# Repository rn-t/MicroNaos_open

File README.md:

# MicroNaos_open
マイクロマウスというロボット競技の、クラシックマウス部門用のロボットです。

## ディレクトリ
### DXF

基板外形のDXFファイルです

### firmware
STM32向けのソースコードです。主にC++で記述しています。STM32HAL、CMSIS、SEGGER-RTTなどのライブラリも含まれています。

### PCB
機体の大部分を構成しているプリント基板及び、その回路のファイルです。Kicadを用いて作成しました
公開するにあたってライセンスの問題がないように編集を行ったため、回路シンボルが基板発注時と少し異なっています。

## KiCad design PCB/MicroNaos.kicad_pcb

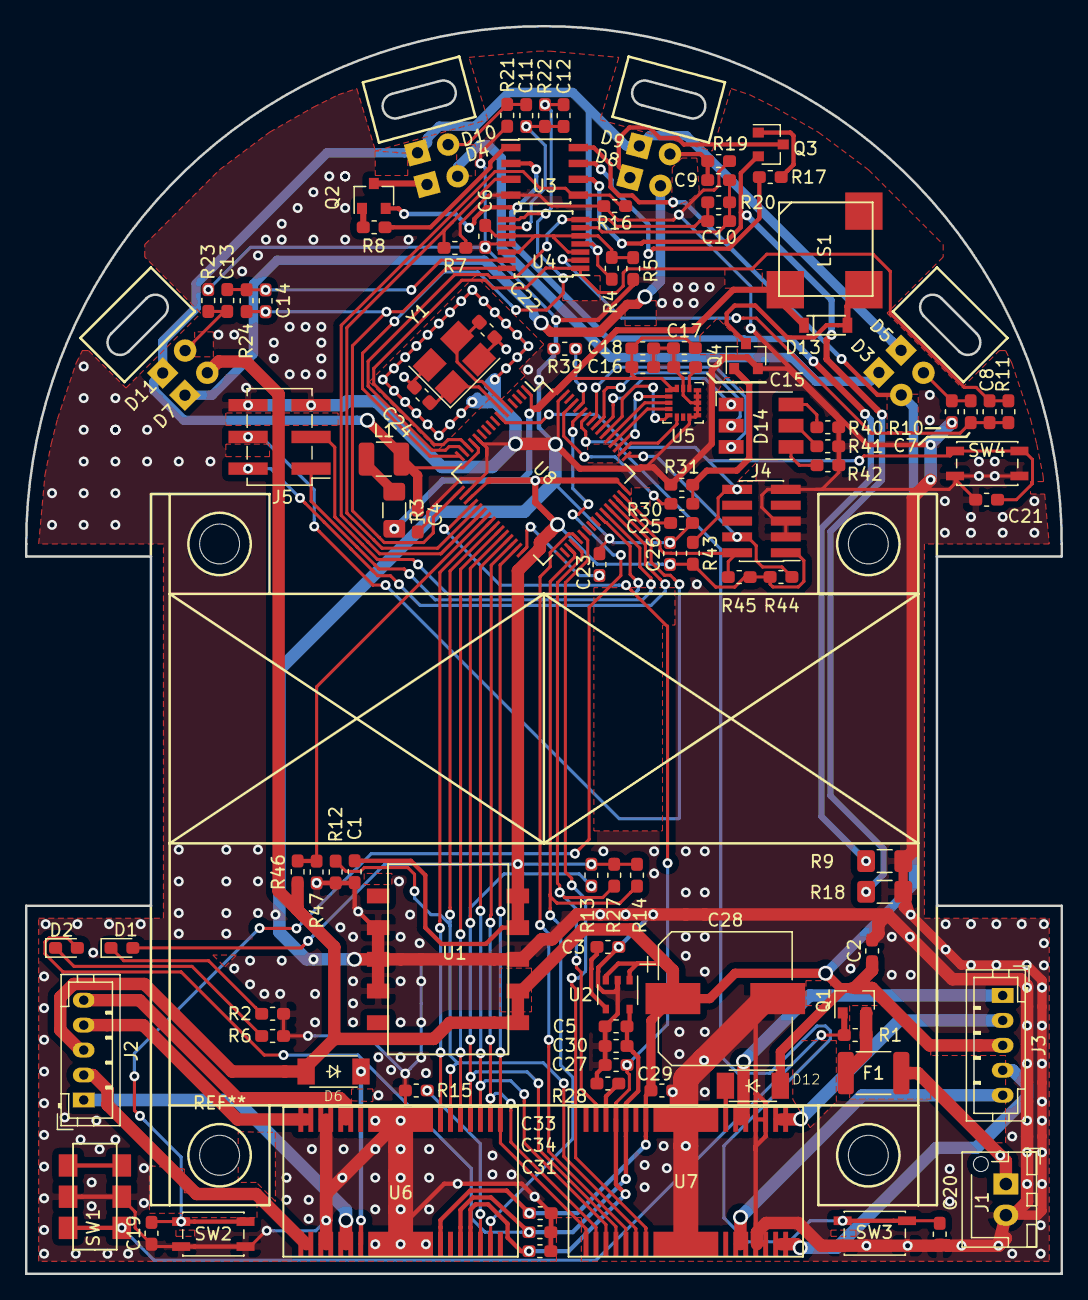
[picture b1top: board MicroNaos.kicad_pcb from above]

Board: 2 copper layers, 83.0 x 100.0 mm, 109 parts (0 on the bottom side), 91 nets.

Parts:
C1: 3.3u; C_0603_1608Metric_Pad1.05x0.95mm_HandSolder
C2: 1u; C_0603_1608Metric_Pad1.05x0.95mm_HandSolder
C3, C7, C9, C11, C13, C16: 0.01u; C_0603_1608Metric_Pad1.05x0.95mm_HandSolder
C4, C5: 10u; C_0603_1608Metric_Pad1.05x0.95mm_HandSolder
C6, C15, C17, C19, C20, C21, C26: 0.1u; C_0603_1608Metric_Pad1.05x0.95mm_HandSolder
C8, C10, C12, C14: 22p; C_0603_1608Metric_Pad1.05x0.95mm_HandSolder
C18, C23, C25: 2.2u; C_0603_1608Metric_Pad1.05x0.95mm_HandSolder
C22, C24: 10p; C_0603_1608Metric_Pad1.05x0.95mm_HandSolder
C27, C29, C30, C31, C33, C34: 0.1uF; C_0603_1608Metric_Pad1.05x0.95mm_HandSolder
C28: 100uF; CP_Elec_10x10.5
D1: LED_3.3V; LED_0603_1608Metric_Pad1.05x0.95mm_HandSolder
D2: LED_5V; LED_0603_1608Metric_Pad1.05x0.95mm_HandSolder
D3, D4, D7, D8: VSLY5850; LED_D5.0mm_Sensor
D5, D9, D10, D11: SFH213FA; LED_D5.0mm_Sensor
D6, D12: 24V1W; SOD128
D13: GS1010FL; SOD-123FL
D14: OSTBABS4C2B; LED_RGB_5050-6
F1: SMD1812P150TF/24; Fuse_1812_4532Metric_Pad1.30x3.40mm_HandSolder
J1: BATTERY; JST_XH_B02B-XH-AM_1x02_P2.50mm_Vertical
J2, J3: PH_5Pin; JST_PH_B5B-PH-K_1x05_P2.00mm_Vertical
J4: Conn_ARM_JTAG_SWD_10; PinHeader_2x05_P1.27mm_Vertical_SMD
J5: Conn_02x03_Odd_Even; PinHeader_2x03_P2.54mm_Vertical_SMD
L1: 100u; L_1210_3225Metric
LS1: Speaker; UGCT7525AN4
Q1: IRLML6402; SOT-23
Q2, Q3, Q4: IRFML8244; SOT-23
R1, R10, R19, R21, R23: 100k; R_0603_1608Metric_Pad1.05x0.95mm_HandSolder
R2, R6: 1k; R_0603_1608Metric_Pad1.05x0.95mm_HandSolder
R3: 10; R_1206_3216Metric_Pad1.42x1.75mm_HandSolder
R4, R5: 1k 1%; R_0603_1608Metric_Pad1.05x0.95mm_HandSolder
R7, R12, R13, R14, R15, R16, R27, R28, R31, R39, R43, R44, R45, R47: 10k; R_0603_1608Metric_Pad1.05x0.95mm_HandSolder
R8, R17: 10; R_0603_1608Metric_Pad1.05x0.95mm_HandSolder
R9, R18: 33 1% 1/2W; R_1206_3216Metric_Pad1.42x1.75mm_HandSolder
R11, R20, R22, R24: 220k; R_0603_1608Metric_Pad1.05x0.95mm_HandSolder
R30: 100; R_0603_1608Metric_Pad1.05x0.95mm_HandSolder
R40, R41, R42: 330; R_0603_1608Metric_Pad1.05x0.95mm_HandSolder
R46: 33k; R_0603_1608Metric_Pad1.05x0.95mm_HandSolder
SW1: SSSS213202
SW2, SW3, SW4: SKRPACE010; SW_SPST_EVQP2
U1: M78SAR033-0.5
U2: TAR5SB50; TSOP-5_1.65x3.05mm_P0.95mm
U3: NJM2746E; SOIC-8_3.9x4.9mm_P1.27mm
U4: AD8604A; TSSOP-14_4.4x5mm_P0.65mm
U5: ICM-20602; LGA-16_3x3mm_P0.5mm_LayoutBorder3x5y
U6, U7: TB67S149FG; HSOP28-P-0450-0.80
U8: STM32F405RGTx; LQFP-64_10x10mm_P0.5mm
Y1: 12MHz; Crystal_SMD_SeikoEpson_FA238V-4Pin_3.2x2.5mm_HandSoldering

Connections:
1.65V: C6.1, R4.2, R5.1, U4.3 (+), U4.5 (+), U4.10 (+), U4.12 (+)
3.3V: C1.1, C16.1, C17.1, C18.1, C26.2, D1.2 (A), D13.1 (K), J4.1 (VTref), LS1.1, R3.2, R13.1, R14.1, R27.1, R43.1, R44.1, R45.1, U1.4 (Vout), U1.5 (Vout), U5.1 (VDDIO), U5.16 (VDD), U8.1 (VBAT), U8.19 (VDD), U8.32 (VDD), U8.48 (VDD), U8.64 (VDD)
3.3VA: C4.1, D5.1 (K), D9.1 (K), D10.1 (K), D11.1 (K), L1.2, R4.1, U4.4 (V+), U8.13 (VDDA)
5V: C5.1, C30.1, C34.1, D2.2 (A), U2.5 (Vout), U6.24 (VCC), U7.24 (VCC)
/Gyro/CS: U5.5 (~CS), U8.54 (PD2)
/Gyro/INT: U5.6 (INT), U8.50 (PA15)
/Gyro/SDI: U5.3 (SDA/SDI), U8.53 (PC12)
/Gyro/SDO: U5.4 (SAO/SD0), U8.52 (PC11)
/Gyro/SPC: U5.2 (SCL/SPC), U8.51 (PC10)
/IR_LED1/LED_IN: R7.2, U3.3 (+), U8.21 (PA5)
/IR_LED2/LED_IN: R16.2, U3.5 (+), U8.22 (PA6)
/IR_Sensor1/SENSOR_OUT: C8.1, R11.1, U4.1, U8.14 (PA0)
/IR_Sensor2/SENSOR_OUT: C10.1, R20.1, U4.7, U8.15 (PA1)
/IR_Sensor3/SENSOR_OUT: C12.1, R22.1, U4.8, U8.16 (PA2)
/IR_Sensor4/SENSOR_OUT: C14.1, R24.1, U4.14, U8.17 (PA3)
/Micon/BATT_CHECK: R46.2, R47.1, U8.23 (PA7)
/Micon/DAC: C27.1, C31.1, U6.25 (VREF), U7.25 (VREF), U8.20 (PA4)
/Micon/MOTOR1_CW: U6.7 (CW/CCW), U8.24 (PC4)
/Micon/MOTOR1_ERR: R14.2, U6.27 (ERR), U8.35 (PB14)
/Micon/MOTOR1_PWM: U6.5 (CLK), U8.26 (PB0)
/Micon/MOTOR2_CW: U7.7 (CW/CCW), U8.38 (PC7)
/Micon/MOTOR2_ERR: R27.2, U7.27 (ERR), U8.36 (PB15)
/Micon/MOTOR2_PWM: U7.5 (CLK), U8.37 (PC6)
/Micon/MOTOR_DMODE0: U6.1 (DMODE0), U7.1 (DMODE0), U8.30 (PB11)
/Micon/MOTOR_DMODE1: U6.2 (DMODE1), U7.2 (DMODE1), U8.29 (PB10)
/Micon/MOTOR_DMODE2: U6.3 (DMODE2), U7.3 (DMODE2), U8.28 (PB2)
/Micon/MOTOR_EN: R12.1, U6.6 (ENABLE), U7.6 (ENABLE), U8.25 (PC5)
/Micon/MOTOR_RESET: R13.2, U6.4 (RESET), U7.4 (RESET), U8.27 (PB1)
/Micon/NRST: C21.2, J4.10 (~RESET), R43.2, SW4.1, U8.7 (NRST)
/Micon/PB8_SPEAKER: R30.2, U8.61 (PB8)
/Micon/SWCLK: J4.4 (SWDCLK/TCK), R44.2, U8.49 (PA14)
/Micon/SWDIO: J4.2 (SWDIO/TMS), R45.2, U8.46 (PA13)
/Micon/SW_1: C20.2, SW3.1, U8.58 (PB6)
/Micon/SW_2: C19.2, SW2.1, U8.59 (PB7)
/Micon/UART_RX: J5.1, U8.43 (PA10)
/Micon/UART_TX: J5.3, U8.42 (PA9)
/Micon/USB_DM: J5.2, U8.44 (PA11)
/Micon/USB_DP: J5.4, U8.45 (PA12)
BATT: C2.1, C28.1, C29.1, C33.1, D3.2 (A), D6.2 (A), D7.2 (A), D12.2 (A), J2.3, J3.3, Q1.3 (D), R46.1, U1.1 (Vin), U1.2 (Vin), U2.1 (Vin), U2.3 (Control), U3.8 (V+), U6.22 (VM), U7.22 (VM)
GND: C1.2, C2.2, C3.2, C4.2, C5.2, C6.2, C15.2, C16.2, C17.2, C18.2, C19.1, C20.1, C21.1, C22.2, C23.1, C24.2, C25.1, C26.1, C27.2, C28.2, C29.2, C30.2, C31.2, C33.2, C34.2, J1.2, J4.3 (GND), J4.5 (GND), J4.9 (GNDDetect), J5.5, J5.6, Q4.2 (S), R2.2, R5.2, R6.2, R7.1, R9.2, R10.1, R12.2, R15.2, R16.1, R18.2, R19.1, R21.1, R23.1, R28.2, R31.1, R39.2, R40.1, R41.1, R42.1, R47.2, SW1.2 (B), SW2.2, SW3.2, SW4.2, U1.3 (GND), U1.7 (GND), U1.8 (GND), U1.9 (GND), U2.2 (GND), U3.4 (V-), U4.11 (V-), U5.8 (FSYNC), U5.9 (GND), U5.10 (GND), U5.11 (GND), U5.12 (GND), U5.13 (GND), U5.15 (GND), U6.11 (RSGNDA), U6.12 (RSGNDA), U6.17 (RSGNDB), U6.18 (RSGNDB), U6.FIN1 (GND), U6.FIN2 (GND), U7.11 (RSGNDA), U7.12 (RSGNDA), U7.17 (RSGNDB), U7.18 (RSGNDB), U7.FIN1 (GND), U7.FIN2 (GND), U8.12 (VSSA), U8.18 (VSS), U8.63 (VSS), Y1.2, Y1.4
unnamed: C3.1, U2.4 (Noise)
unnamed: C7.1, C8.2, R11.2, U4.2 (-)
unnamed: C7.2, D5.2 (A), R10.2
unnamed: C9.2, D9.2 (A), R19.2
unnamed: C9.1, C10.2, R20.2, U4.6 (-)
unnamed: C11.1, C12.2, R22.2, U4.9 (-)
unnamed: C11.2, D10.2 (A), R21.2
unnamed: C13.1, C14.2, R24.2, U4.13 (-)
unnamed: C13.2, D11.2 (A), R23.2
unnamed: C15.1, U5.14 (REGOUT)
unnamed: C22.1, U8.5 (PH0), Y1.3
unnamed: C23.2, U8.31 (VCAP_1)
unnamed: C24.1, U8.6 (PH1), Y1.1
unnamed: C25.2, U8.47 (VCAP_2)
unnamed: D1.1 (K), R2.1
unnamed: D2.1 (K), R6.1
unnamed: D3.1 (K), D4.2 (A)
unnamed: D4.1 (K), Q2.3 (D)
unnamed: D6.1 (K), U6.21 (VCOM)
unnamed: D7.1 (K), D8.2 (A)
unnamed: D8.1 (K), Q3.3 (D)
unnamed: D12.1 (K), U7.21 (VCOM)
unnamed: D13.2 (A), LS1.2, Q4.3 (D)
unnamed: D14.1 (BA), U8.55 (PB3)
unnamed: D14.2 (GA), U8.56 (PB4)
unnamed: D14.3 (RA), U8.57 (PB5)
unnamed: D14.4 (RK), R42.2
unnamed: D14.5 (GK), R41.2
unnamed: D14.6 (BK), R40.2
unnamed: F1.1, Q1.2 (S), R1.1
unnamed: F1.2, J1.1
unnamed: J2.1, U6.19 (OUTB+), U6.20 (OUTB+)
unnamed: J2.2, U6.16 (OUTB-)
unnamed: J2.4, U6.13 (OUTA-)
unnamed: J2.5, U6.9 (OUTA+), U6.10 (OUTA+)
unnamed: J3.1, U7.19 (OUTB+), U7.20 (OUTB+)
unnamed: J3.2, U7.16 (OUTB-)
unnamed: J3.4, U7.13 (OUTA-)
unnamed: J3.5, U7.9 (OUTA+), U7.10 (OUTA+)
unnamed: L1.1, R3.1
unnamed: Q1.1 (G), R1.2, SW1.1 (A)
unnamed: Q2.1 (G), R8.1
unnamed: Q2.2 (S), R9.1, U3.2 (-)
unnamed: Q3.1 (G), R17.1
unnamed: Q3.2 (S), R18.1, U3.6 (-)
unnamed: Q4.1 (G), R30.1, R31.2
unnamed: R8.2, U3.1
unnamed: R15.1, U6.26 (OSCM)
unnamed: R17.2, U3.7
unnamed: R28.1, U7.26 (OSCM)
unnamed: R39.1, U8.60 (BOOT0)

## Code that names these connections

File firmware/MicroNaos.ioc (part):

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Mcu.Name=STM32F405RGTx
Mcu.Package=LQFP64
Mcu.UserName=STM32F405RGTx
PA0-WKUP.Signal=ADCx_IN0
PA1.Signal=ADCx_IN1
PA10.Mode=Asynchronous
PA10.Signal=USART1_RX
PA11.Mode=Device_Only
PA11.Signal=USB_OTG_FS_DM
PA12.Mode=Device_Only
PA12.Signal=USB_OTG_FS_DP
PA13.Mode=Serial_Wire
PA13.Signal=SYS_JTMS-SWDIO
PA14.Mode=Serial_Wire
PA14.Signal=SYS_JTCK-SWCLK
PA15.GPIOParameters=GPIO_Label
PA15.GPIO_Label=GYRO_IN
PA15.Signal=GPIO_Input
PA2.Signal=ADCx_IN2
PA3.Signal=ADCx_IN3
PA4.GPIOParameters=GPIO_Label
PA4.GPIO_Label=DAC
PA4.Signal=COMP_DAC1_group
PA5.GPIOParameters=GPIO_Label
PA5.GPIO_Label=IR_LED1
PA5.Signal=S_TIM2_CH1_ETR
PA6.GPIOParameters=GPIO_Label
PA6.GPIO_Label=IR_LED2
PA6.Signal=S_TIM13_CH1
PA7.GPIOParameters=GPIO_Label
PA7.GPIO_Label=BATT_CHECK
PA7.Signal=ADCx_IN7
PA9.Mode=Asynchronous
PA9.Signal=USART1_TX
PB0.GPIOParameters=GPIO_Label
PB0.GPIO_Label=MOTOR1_PWM
PB0.Signal=S_TIM3_CH3
PB1.GPIOParameters=GPIO_Label
PB1.GPIO_Label=MOTOR_RESET
PB1.Signal=GPIO_Output
PB10.GPIOParameters=GPIO_Label
PB10.GPIO_Label=MOTOR_DMODE1
PB10.Signal=GPIO_Output
PB11.GPIOParameters=GPIO_Label
PB11.GPIO_Label=MOTOR_DMODE0
PB11.Signal=GPIO_Output
PB14.GPIOParameters=GPIO_Label
PB14.GPIO_Label=MOTOR1_ERR
PB14.Signal=GPIO_Input
PB15.GPIOParameters=GPIO_Label
PB15.GPIO_Label=MOTOR2_ERR
PB15.Signal=GPIO_Input
PB2.GPIOParameters=GPIO_Label
PB2.GPIO_Label=MOTOR_DMODE2
PB2.Signal=GPIO_Output
PB3.GPIOParameters=GPIO_Label
PB3.GPIO_Label=LED_B
PB3.Signal=GPIO_Output
PB4.GPIOParameters=GPIO_Label
PB4.GPIO_Label=LED_G
PB4.Signal=GPIO_Output
PB5.GPIOParameters=GPIO_Label
PB5.GPIO_Label=LED_R
PB5.Signal=GPIO_Output
PB6.GPIOParameters=GPIO_PuPd,GPIO_Label
PB6.GPIO_Label=SW_1
PB6.GPIO_PuPd=GPIO_PULLUP
PB6.Signal=GPIO_Input
PB7.GPIOParameters=GPIO_PuPd,GPIO_Label
PB7.GPIO_Label=SW_2
PB7.GPIO_PuPd=GPIO_PULLUP
PB7.Signal=GPIO_Input
PB8.GPIOParameters=GPIO_Label
PB8.GPIO_Label=SPEAKER
PB8.Signal=S_TIM10_CH1
PC10.Mode=Full_Duplex_Master
PC10.Signal=SPI3_SCK
PC11.Mode=Full_Duplex_Master
PC11.Signal=SPI3_MISO
PC12.Mode=Full_Duplex_Master
PC12.Signal=SPI3_MOSI
PC4.GPIOParameters=GPIO_Label
PC4.GPIO_Label=MOTOR1_CW
PC4.Signal=GPIO_Output
PC5.GPIOParameters=GPIO_Label
PC5.GPIO_Label=MOTOR_EN
PC5.Signal=GPIO_Output
PC6.GPIOParameters=GPIO_Label
PC6.GPIO_Label=MOTOR2_PWM
PC6.Signal=S_TIM8_CH1
PC7.GPIOParameters=GPIO_Label
PC7.GPIO_Label=MOTOR2_CW
PC7.Signal=GPIO_Output
PD2.GPIOParameters=GPIO_Label
PD2.GPIO_Label=SPI_CS
PD2.Signal=GPIO_Output
PH0-OSC_IN.Mode=HSE-External-Oscillator
PH0-OSC_IN.Signal=RCC_OSC_IN
PH1-OSC_OUT.Mode=HSE-External-Oscillator
PH1-OSC_OUT.Signal=RCC_OSC_OUT
RCC.HSE_VALUE=12000000
RCC.SYSCLKFreq_VALUE=168000000
RCC.SYSCLKSource=RCC_SYSCLKSOURCE_PLLCLK
board=custom

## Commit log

2022-11-04 README.mdにロボット画像を追加
2022-11-06 書き換えを行った。
2022-11-06 Mazelibraryをsubmoduleとして追加
2022-11-06 Mazelibraryを更新
2022-11-06 迷路関係についてはmazelibraryに任せることにした
2022-11-06 コンパイルができるようになったが、 has a LOAD segment with RWX permissions という警告も出た
2022-11-06 向きと見えた壁からマップ情報で使う壁を返す関数を作成した
2022-11-06 mazelibraryの更新を反映した
2022-11-06 コンパイルと動作を確認した 電流値を少し上げた
2022-11-13 とりあえず動いた。角度の補正が必要。
2022-11-13 ジャイロを使った補正を入れた
2022-11-18 3,3にゴールできた。壁補正を入れたい
2022-11-19 壁補正を無効化した
2022-11-20 回転をジャイロで行うようにした
2022-11-20 ゴールはできたが、step==3の帰り道でコケる
2022-12-25 大会の(たぶん)
2023-02-10 直進時にブレーキをかけない状態を作った。
2023-02-11 絶対パスになっており、フォルダ名まで異なっていたので更新
2023-02-11 うまく動かないため、makefile-toolsを使わないように変更
2023-02-11 プロトタイプ宣言と実体の宣言で両方デフォルト引数を定義していたエラーを修正
2023-02-11 flashのsector0に迷路データを保存できるように書き換え
2023-02-11 flashの読み書きを実装した
2023-02-14 jlinkで書き込みだけをできるようにした
2023-02-14 簡単な壁補正を入れた
2023-02-14 flashによる壁の保存を追加 探索を往復足立法に変更した
2023-02-14 省略可能なvoidを削除
2023-02-14 手法を往復足立法に変更した
2023-02-22 全日本2022の時のプログラム
2023-11-11 東日本大会のやつ
